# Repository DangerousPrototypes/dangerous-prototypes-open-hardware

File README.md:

# dangerous-prototypes-open-hardware
Automatically exported from code.google.com/p/dangerous-prototypes-open-hardware

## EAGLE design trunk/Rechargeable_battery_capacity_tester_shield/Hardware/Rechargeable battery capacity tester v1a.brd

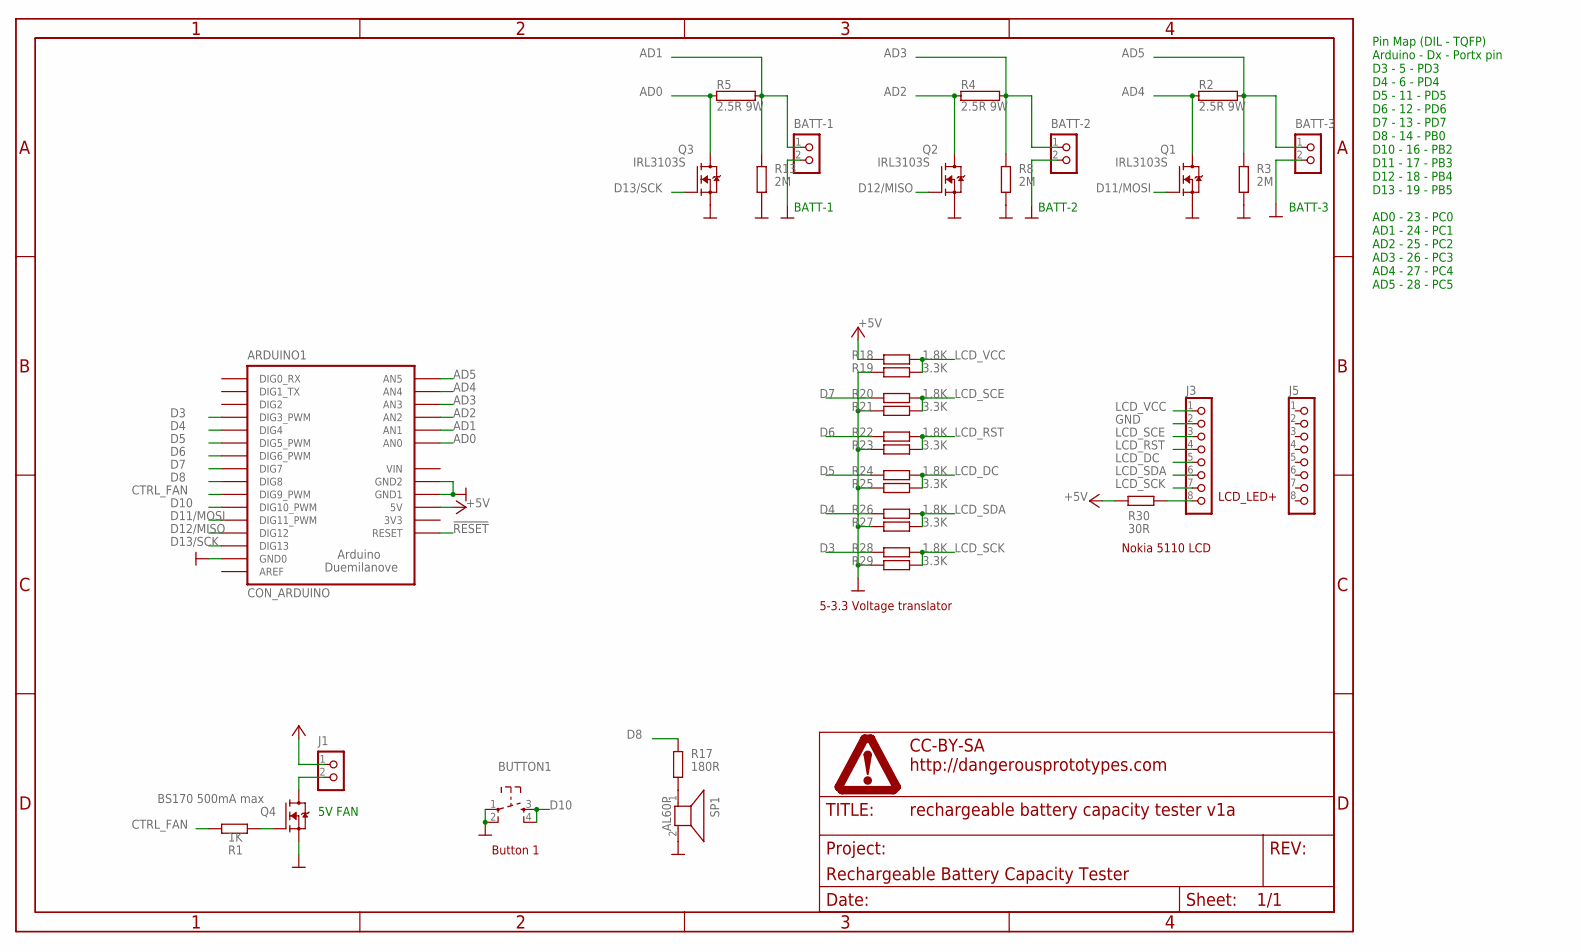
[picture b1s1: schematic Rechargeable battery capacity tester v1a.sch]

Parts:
ARDUINO1: CON_ARDUINO
BATT-1, BATT-2, BATT-3: CON_TERMINAL_BLOCK_02-5MM; TERMINAL_BLOCK_2P_5
BUTTON1: SW_TACT_4P; SW_TACT_SMALL
J1: CON_JST_2PIN-PTH; CON_JST_2PIN
J3, J5: CON_HEADER_1X08-PTH; M1X8
Q1, Q2, Q3: IRL3103S; D2PAK
Q4: BS170 500mA max; SOT-23
R1: 1K; R603
R2, R4, R5: 2.5R 9W; KH214-8
R3, R8, R13: 2M; R603
R17: 180R; R603
R18, R20, R22, R24, R26, R28: 1.8K; R603
R19, R21, R23, R25, R27, R29: 3.3K; R603
R30: 30R; R603
SP1: AL60P
U$1: FRAME_DINA4_L; DP_LOGO

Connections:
!RESET: ARDUINO1.RESET
+5V: ARDUINO1.5V, J1.1, R18.1, R30.1
AD0: ARDUINO1.A_0 (AN0), Q3.2 (D), R5.1
AD1: ARDUINO1.A_1 (AN1), BATT-1.1, R5.2, R13.2
AD2: ARDUINO1.A_2 (AN2), Q2.2 (D), R4.1
AD3: ARDUINO1.A_3 (AN3), BATT-2.1, R4.2, R8.2
AD4: ARDUINO1.A_4 (AN4), Q1.2 (D), R2.1
AD5: ARDUINO1.A_5 (AN5), BATT-3.1, R2.2, R3.2
CTRL_FAN: ARDUINO1.D_9 (DIG9_PWM), R1.1
D3: ARDUINO1.D_3 (DIG3_PWM), R28.1
D4: ARDUINO1.D_4 (DIG4), R26.1
D5: ARDUINO1.D_5 (DIG5_PWM), R24.1
D6: ARDUINO1.D_6 (DIG6_PWM), R22.1
D7: ARDUINO1.D_7 (DIG7), R20.1
D8: ARDUINO1.D_8 (DIG8), R17.2
D10: ARDUINO1.D_10 (DIG10_PWM), BUTTON1.3, BUTTON1.4
D11/MOSI: ARDUINO1.D_11 (DIG11_PWM), Q1.1 (G)
D12/MISO: ARDUINO1.D_12 (DIG12), Q2.1 (G)
D13/SCK: ARDUINO1.D_13 (DIG13), Q3.1 (G)
GND: ARDUINO1.GND0, ARDUINO1.GND1, ARDUINO1.GND2, BATT-1.2, BATT-2.2, BATT-3.2, BUTTON1.1, BUTTON1.2, J3.2, Q1.3 (S), Q2.3 (S), Q3.3 (S), Q4.2 (S), R3.1, R8.1, R13.1, R19.1, R21.1, R23.1, R25.1, R27.1, R29.1, SP1.2
LCD_DC: J3.5, R24.2, R25.2
LCD_RST: J3.4, R22.2, R23.2
LCD_SCE: J3.3, R20.2, R21.2
LCD_SCK: J3.7, R28.2, R29.2
LCD_SDA: J3.6, R26.2, R27.2
LCD_VCC: J3.1, R18.2, R19.2
unnamed: Q4.1 (G), R1.2
unnamed: J1.2, Q4.3 (D)
unnamed: J3.8, R30.2
unnamed: R17.1, SP1.1
VIN: ARDUINO1.VIN

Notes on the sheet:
Pin Map (DIL - TQFP) Arduino - Dx - Portx pin D3 - 5 - PD3 D4 - 6 - PD4 D5 - 11 - PD5 D6 - 12 - PD6 D7 - 13 - PD7 D8 - 14 - PB0 D10 - 16 - PB2 D11 - 17 - PB3 D12 - 18 - PB4 D13 - 19 - PB5 AD0 - 23 - PC0 AD1 - 24 - PC1 AD2 - 25 - PC2 AD3 - 26 - PC3 AD4 - 27 - PC4 AD5 - 28 - PC5
BATT-3
BATT-2
BATT-1
Button 1
LCD_LED+
Nokia 5110 LCD
5-3.3 Voltage translator
5V FAN

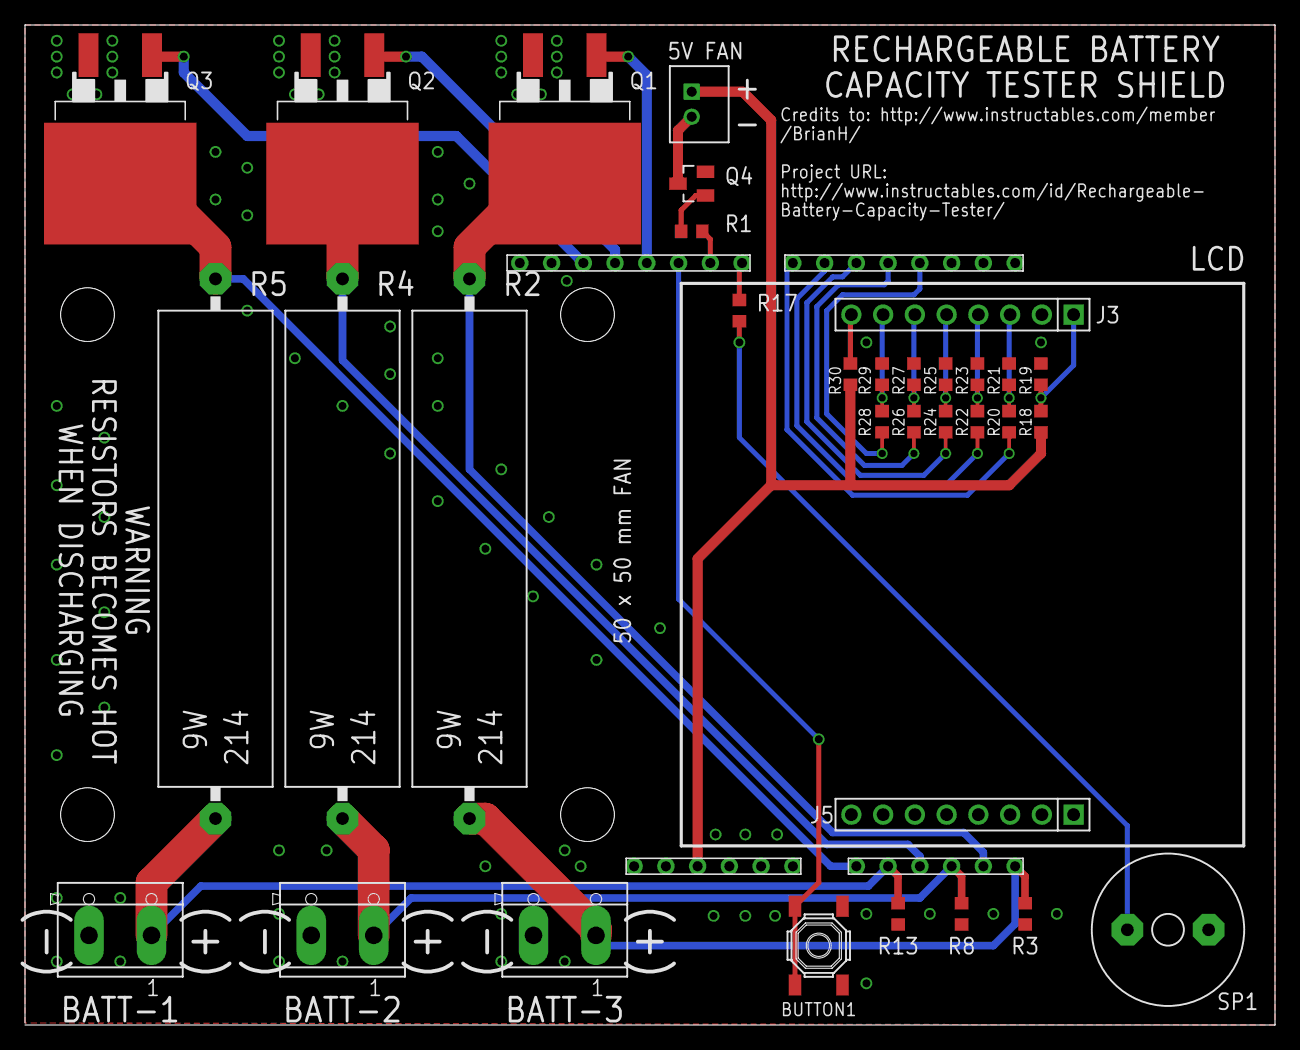
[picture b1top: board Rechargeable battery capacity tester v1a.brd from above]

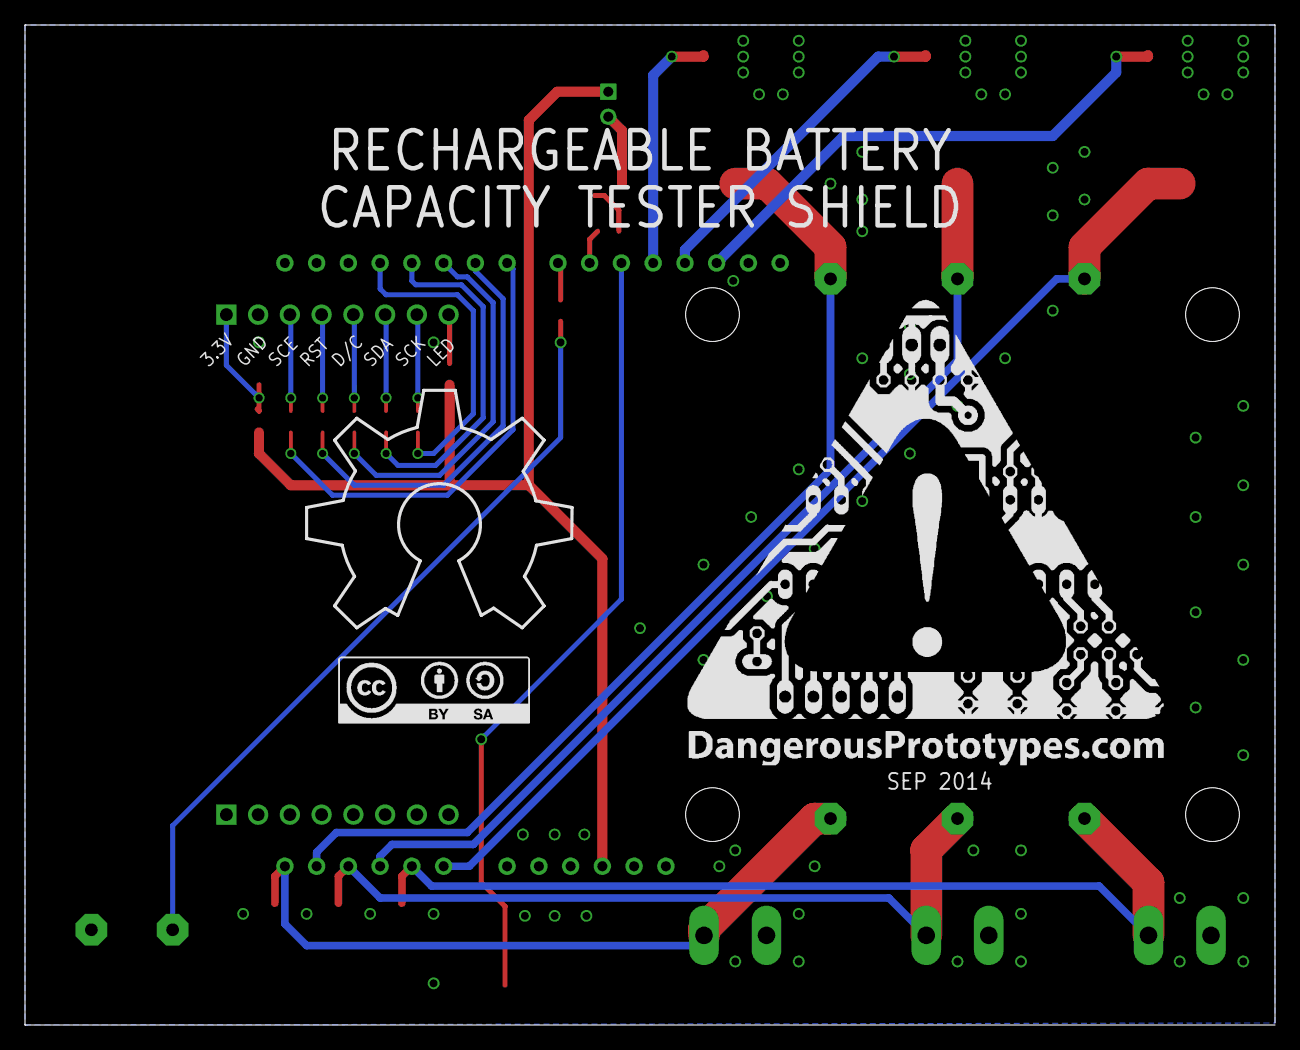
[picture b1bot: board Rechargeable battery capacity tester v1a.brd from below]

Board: 2 copper layers, 100.0 x 80.0 mm, 38 parts (3 on the bottom side), 29 nets.

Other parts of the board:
U$2: DP_LOGO_ART_1.5X1.5
U$3: LOGO_CC-BY-SA
U$4: OSHW_10X750_NOTEXT

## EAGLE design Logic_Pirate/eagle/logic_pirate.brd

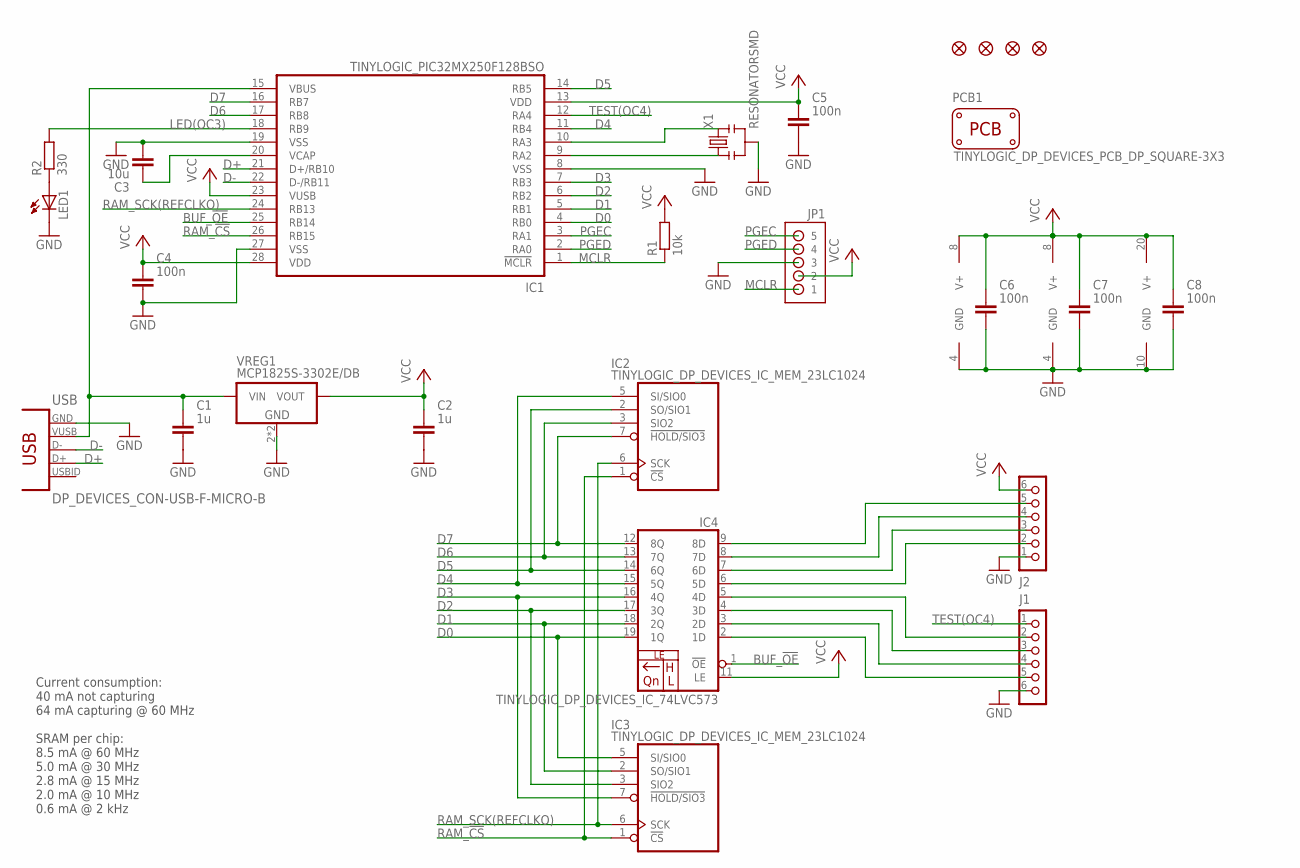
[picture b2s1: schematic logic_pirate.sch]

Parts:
C1, C2: 1u; DP_DEVICES_C603
C3: 10u; C1206
C4, C5, C6, C7, C8: 100n; DP_DEVICES_C603
IC1: TINYLOGIC_PIC32MX250F128BSO; TINYLOGIC_DP_DEVICES_SOIC-28W
IC2, IC3: TINYLOGIC_DP_DEVICES_IC_MEM_23LC1024; TINYLOGIC_DP_DEVICES_SOIC-8
IC4: TINYLOGIC_DP_DEVICES_IC_74LVC573; TINYLOGIC_DP_DEVICES_SOIC-20
J1, J2: DP_DEVICES_CON_HEADER_1X06-SMD-RIGHT-ANGLED; DP_DEVICES_M1X6_MALE_RIGHT_ANGLED_SMD
JP1: TINYLOGIC_CHIPKIT_UNO32_MECHANICAL_HDR-1X5-OFFSET; TINYLOGIC_CHIPKIT_UNO32_MECHANICAL_HDR-1X6_OFFSET
JP2, JP3, JP4, JP5: FIDUCIAL1X2; FIDUCIAL-1X2
LED1: Status; CHIPKIT_UNO32_DISCRETE_D0603
PCB1: TINYLOGIC_DP_DEVICES_PCB_DP_SQUARE-3X3; TINYLOGIC_DP_DEVICES_DP3030_V1
R1: 10k; DP_DEVICES_R603
R2: 330; DP_DEVICES_R603
USB: DP_DEVICES_CON-USB-F-MICRO-B; DP_DEVICES_CONN_USB_MICRO-B
VREG1: MCP1825S-3302E/DB; DP_DEVICES_SOT-223
X1: RESONATORSMD; RESONATOR-SMD

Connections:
BUF_!OE!: IC1.25 (RB14), IC4.1 (!OE)
D0: IC1.4 (RB0), IC3.5 (SI/SIO0), IC4.19 (1Q)
D1: IC1.5 (RB1), IC3.2 (SO/SIO1), IC4.18 (2Q)
D2: IC1.6 (RB2), IC3.3 (SIO2), IC4.17 (3Q)
D3: IC1.7 (RB3), IC3.7 (!HOLD/SIO3), IC4.16 (4Q)
D4: IC1.11 (RB4), IC2.5 (SI/SIO0), IC4.15 (5Q)
D5: IC1.14 (RB5), IC2.2 (SO/SIO1), IC4.14 (6Q)
D6: IC1.17 (RB8), IC2.3 (SIO2), IC4.13 (7Q)
D7: IC1.16 (RB7), IC2.7 (!HOLD/SIO3), IC4.12 (8Q)
D+: IC1.21 (D+/RB10), USB.P3 (D+)
D-: IC1.22 (D-/RB11), USB.P2 (D-)
GND: C1.2, C2.2, C3.2, C4.2, C5.2, C6.2, C7.2, C8.2, IC1.8 (VSS), IC1.19 (VSS), IC1.27 (VSS), IC2.4 (GND), IC3.4 (GND), IC4.10 (GND), J1.6, J2.1, JP1.3, LED1.C, USB.P5 (GND), VREG1.2 (GND), VREG1.4 (GND), X1.2
LED(OC3): IC1.18 (RB9), R2.2
MCLR: IC1.1 (!MCLR), JP1.1, R1.1
unnamed: IC4.2 (1D), J1.5
unnamed: IC4.3 (2D), J1.4
unnamed: IC4.4 (3D), J1.3
unnamed: IC4.5 (4D), J1.2
unnamed: IC4.6 (5D), J2.2
unnamed: IC4.7 (6D), J2.3
unnamed: IC4.8 (7D), J2.4
unnamed: IC4.9 (8D), J2.5
unnamed: LED1.A, R2.1
unnamed: IC1.10 (RA3), X1.3
unnamed: IC1.9 (RA2), X1.1
unnamed: C3.1, IC1.20 (VCAP)
PGEC: IC1.3 (RA1), JP1.5
PGED: IC1.2 (RA0), JP1.4
RAM_!CS!: IC1.26 (RB15), IC2.1 (!CS), IC3.1 (!CS)
RAM_SCK(REFCLKO): IC1.24 (RB13), IC2.6 (SCK), IC3.6 (SCK)
TEST(OC4): IC1.12 (RA4), J1.1
VBUS: C1.1, IC1.15 (VBUS), USB.P1 (VUSB), VREG1.1 (VIN)
VCC: C2.1, C4.1, C5.1, C6.1, C7.1, C8.1, IC1.13 (VDD), IC1.23 (VUSB), IC1.28 (VDD), IC2.8 (V+), IC3.8 (V+), IC4.11 (LE), IC4.20 (V+), J2.6, JP1.2, R1.2, VREG1.3 (VOUT)

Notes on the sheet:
Current consumption: 40 mA not capturing 64 mA capturing @ 60 MHz SRAM per chip: 8.5 mA @ 60 MHz 5.0 mA @ 30 MHz 2.8 mA @ 15 MHz 2.0 mA @ 10 MHz 0.6 mA @ 2 kHz

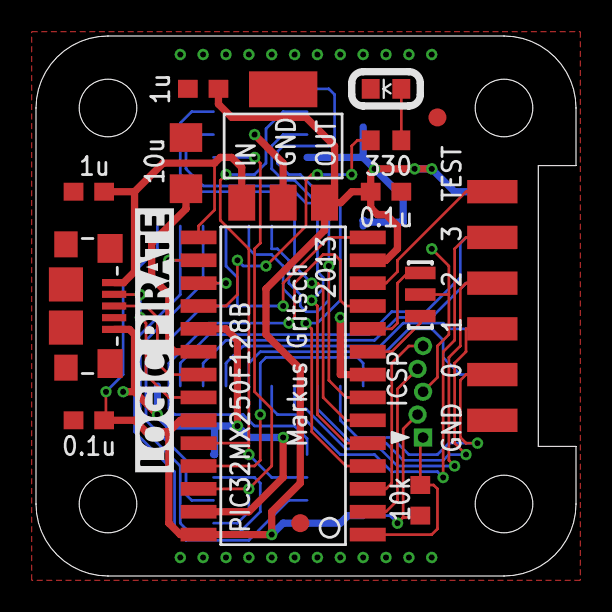
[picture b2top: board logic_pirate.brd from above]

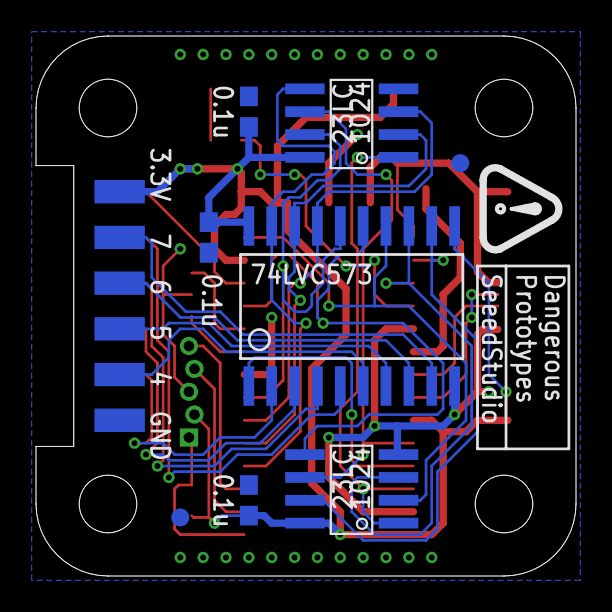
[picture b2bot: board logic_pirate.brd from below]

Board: 2 copper layers, 30.0 x 30.0 mm, 28 parts (10 on the bottom side), 33 nets.

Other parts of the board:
U$1: LP_LOGO
U$4: TINY_LOGO

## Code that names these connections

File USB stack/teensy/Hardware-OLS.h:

/*
*
*	Open Logic Sniffer firmware v1.1
*	http://www.gadgetfactory.net
*	http://dangerousprototypes.com
*	License: GPL
*	Copyright Ian Lesnet 2010
*
*/
#ifndef HARDWARE_PROFILE_H
#define HARDWARE_PROFILE_H

//the first batch of OLS has 20mhz crystal on the PIC
//use this to compile for that hardware
#define XTAL_20MHZ

//hardware version string
#define HW_VER 0x01

//firmware version string
#define FW_VER_H 0x00
#define FW_VER_L 0x06

//Define to enable manufacturing hardware 
//self-test with jumper check on UART header.
//If there is a jumper between RX and TX
//the firmware will light the ACT LED and send 0x03 
//to the FPGA through the UART. THis triggers a test mode
//in special bitstream builds.
#define SELF_TEST	

//measure the voltage on PROG_B (AN3/RA3), should be 2.5volts
#define VREG_TEST
//calculate the ADC value to test for
//#define ADC_2V5 ((25/33)*1024) //2.5volts/3.3volts * 1024 = ADC reading (775.75).
//#define ADC_2V5_LIMIT (ADC_2V5-(ADC_2V5/10)) //show error if not within 10% 775-78=697
#define ADC_2V5_LIMIT 697

//During testing we used a pin for the UART 
// that was sharted with a trigger pin
// some old bitstreams used it and it got confusing
//We had to keep changing it back and forth so I added this define
//There isn't really any reason you should ever need this, 
// especially in the SPI version, but here it is. Enjoy.
//#define OLDRXPIN //use RX on the old pin

//pin setup
/*
A0 PR0 flash_si
A1 PR1 flash_so
A2 flash_cs
A3 PROG_B (pull-down only) test high
A5 RP2 DONE (input only) test high, eventually
C1 RP12 update button (input/interrupt) test high
C2 RP13 ACT LED

B7 RP10 PGD
B6 RP9 PGC
B5 RP8 flash_sck
B4 RP7 FPGA_AUX0
B3 RP6 fpga_cs
B2 RP5 fpga_aux1
B1 RP4 FPGA_AUX2
B0 RP3 FPGA_AUX3
C7 RP18 RX1
C6 RP17 TX1
*/
#define PIN_PROG_B 		PORTAbits.RA3
#define TRIS_PROG_B 	TRISAbits.TRISA3
#define PROG_B_LOW()	PIN_PROG_B=0; TRIS_PROG_B=0 //ground,output
#define PROG_B_HIGH()	PIN_PROG_B=0; TRIS_PROG_B=1	

#define PIN_DONE		PORTAbits.RA5
#define PIN_UPDATE 		PORTCbits.RC1
#define PIN_LED			PORTCbits.RC2

#define TRIS_UART1_TX	TRISCbits.TRISC6
#define PIN_UART1_TX	LATCbits.LATC6
#define TRIS_UART1_RX	TRISCbits.TRISC7
#define PIN_UART1_RX	PORTCbits.RC7
//	#define TRIS_UART1		TRISC
//	#define TXPIN_UART1		0b01000000
//	#define RXPIN_UART1		0b10000000

#define TRIS_UART2_TX	TRISBbits.TRISB1
#define PIN_UART2_TX	PORTBbits.RB1

#define TRIS_FLASH_SCK	TRISBbits.TRISB5
#define PIN_FLASH_SCK	PORTBbits.RB5
#define TRIS_FLASH_MOSI	TRISAbits.TRISA0
#define PIN_FLASH_MOSI	PORTAbits.RA0

#define TRIS_FLASH_CS	TRISAbits.TRISA2
#define PIN_FLASH_CS	PORTAbits.RA2
#define FPGA_CS_LOW()	PIN_FLASH_CS=0; TRIS_FLASH_CS=0
#define FPGA_CS_HIGH() 	PIN_FLASH_CS=1; TRIS_FLASH_CS=0

#define TRIS_FPGA_SCK	TRISBbits.TRISB4
#define PIN_FPGA_SCK	PORTBbits.RB4
#define TRIS_FPGA_MISO	TRISBbits.TRISB2
#define PIN_FPGA_MISO	PORTBbits.RB2
#define TRIS_FPGA_MOSI	TRISBbits.TRISB3
#define PIN_FPGA_MOSI	PORTBbits.RB3
#define TRIS_FPGA_DATAREADY	TRISBbits.TRISB1
#define PIN_FPGA_DATAREADY	PORTBbits.RB1

#define TRIS_FPGA_CS	TRISAbits.TRISA1
#define PIN_FPGA_CS		PORTAbits.RA1

#define BootloaderJump() _asm goto 0x16 _endasm

//these are unneeded, but the stack complains if they're not defined
//#define USE_SELF_POWER_SENSE_IO
#define tris_self_power     TRISCbits.TRISC2    
#define self_power          1

//#define USE_USB_BUS_SENSE_IO
#define tris_usb_bus_sense  TRISCbits.TRISC2    
#define USB_BUS_SENSE       1 

#endif 

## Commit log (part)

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2012-08-14 Changes to USB interrupt from JTR
2012-08-14 small fix to BPv4 bootloader (comment in wrong place)
    http://dangerousprototypes.com/forum/viewtopic.php?f=28&t=3441&start=45#p42466
2012-08-14 Added USB interrupt fix to BPv4 from: http://dangerousprototypes.com/forum/viewtopic.php?f=28&t=3441&start=45#p42038
2012-08-16 Bus Pirate Demo board firmware
2012-08-20 Added device: 23LC1024 SRAM in SOIC-8
2012-08-27 update to blog theme with header fix, switch for contest theme.
2012-08-27 blog theme contest template update
2012-09-04 Added devices: 74HC595 and 74141 Added footprint: DIL16 Updated: removed extra mounting holes on DP6060 Added schematic symbol: 12V, -12V and -5V Added Logo: Flame logo
2012-09-04 revised credit card sized PCB based on ISO.IEC 7810 ID-1 identification cards sizes, size changed from 85 x 56 mm to 85.60 x 53.98 mm
2012-09-05 SU originals for the ATX case laser cutting
2012-09-06 little file reshuffeling in the ATX laser cutt files
2012-09-07 Fix IN-12 socket, replaced with correct cutout.
2012-09-07 Added: IN-12 Nixie tube display, IN-12 Socket cutout footprint Fixed: IN-12 Socket
2012-09-12 Updated ATX PSU v1.3 Added ATX PSU v2 board. Board was made in KiCAD
2012-09-12 first commit of DP KiCAD part library
2012-09-13 .lib and .mod files converted using eagle2kicad-0.d.ulp from http://www.modulbot.com/download.html Fixed undefined DRAW command when loading to symbol library to KiCAD
2012-09-17 add bus pirate v5c board, enlarge ADC Input label
2012-09-20 Bus Pirate v4 Sick of Beige case laser cutting files and partlist(BOM)
2012-09-21 SoB case generator plugin from Tayken
2012-09-24 Done the changes related to global->instance variables suggested by Jim, corrected some variable name typos and got rid of console debug messages.
2012-09-24 Added new Logic shrimp v2b, this version uses 23LC1024 SRAM
2012-09-25 added direction info on birectional buffer ICs
2012-09-25 Board files
2012-09-25 add schematic image
2012-09-27 OHS 2012 presentations
2012-10-01 Smoke Tester 3D model and renders
2012-10-07 Adding a vertical ATX socket from the Molex MiniFit Jr. line.
    Discrete sockets (key'ed and rectangular) are provided in separate files so they can be easily added to create different configurations. Each socket is made to be "stackable" on both sides, so you'll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
2012-10-07 adding an assortment of 3d models. They should all have origins centered properly about the pins. These were not checked thoroughly, but do appear to be generally correct. Most models are tweaked fro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
    The QFN32 is original and should be extremely easy to scale and accommodate other numbers of pins.
2012-10-08 Added: D8035E VFD board, composed of 3 boards. Board A, B and C
2012-10-08 Added: PTH variant of 2.1mm DC Barrel Connector with milled hole pads
2012-10-09 added series diode on Vusb in and Vin header, moved C8 beside SD holder
2012-10-10 first cut at molex KK series connectors. The 1x2 should be modeled in such a way that it's side stackable, so it will be easy to make additional even numbered connectors. These were based on a model 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
    These should be "close enough" for most purposes, alignment appears to be off a bit on the 4pos header though.
2012-10-10 Bourns TC33X-2-104E 3mm surface mount trim pot
2012-10-10 Added: 3D models for 2 trough-hole IC and a metalized Capacitor.
2012-10-11 added version 2
2012-10-16 rearanged SID SVN, and aded the mauf resources and sales page foleder...as wlell as the sales page txt
2012-10-18 correcting the naming for the 2512 resistor model
2012-10-18 adding a 2010 resistor
2012-10-18 Bus Blaster v4 test buffer project
2012-10-18 Bus blaster v3 v4 manufacturing resrouces
2012-10-22 Soldering Iron Driver renderings and 3D model
2012-10-25 Added projects: DP6037 protoboard v1, DP6037_PTH v1 and DP6037_SMD v1
2012-10-25 add: FT230x_LTC4053_BB
2012-10-25 Add project: FT311 breakout board v1b
2012-10-28 Retrieved demo board v5 files from previous revision, and renamed the wrongly named v5a into proper names
2012-10-30 added DIL-28 PTH to SMD socket
2012-10-31 Added manufacturing files for updated ATX board acrylic case
2012-11-05 added: 4.5 x 4.5 SMD Trimmer, model 3314G
2012-11-07 added right angled 0.1inch 1x06 male header. expanded M1X4, M1X6, M1X8 pads to 1.632mm and drill size to 1.02mm
2012-11-13 added a 1x06 right angled header and a 2x03 SMD straight male headers.
2012-11-15 initial xQFP protoboards folder
2012-11-19 BP v4d, buspirate v4 fitted into a bigger DP PCB (DP7043)
2012-11-22 added ICSP with pogo pin as connector
2012-11-22 fix, ICSP pogo pin programmer footprint by adding a pad on the keyhole for a key pogo pin to be soldered
2012-11-30 added 0.50, 0.65 and 0.80 mm pitch universal QFP footprint and QFP breakout board These footprint are licensed: CC-BY-SA
2012-12-06 added protoboard with 0.50mm xQFP
2012-12-06 added protoboard with 0.65mm and 0.80mm xQFP
2012-12-07 updated 0.5, 0.65 and 0.8 xQFP protoboards by adding a USB footprint. 2-3 SOT-23-6 footprints were removed to fit the usb
2012-12-07 widen pad diameter
2012-12-12 added dual xQFP pitch protoboards, pitch combined are 0.50 + 0.65 mm, 0.80 + 0.50 mm and 0.80 + 0.65 mm. these boards were also having a micro usb footprint under its mini-b footprint
2012-12-12 adding dual pitch back to back footprint on xQFP breakout, combined pitch are 0.50 + 0.65, 0.80 + 0.50 and 0.80 + 0.65 mm QFP
2012-12-14 fix pad, changed via to a pad. new board named v1b
2012-12-20 added: 1x1 PTH hole for protoboard filler changed "board name" of DP standard PCB name(on the bottom) to ">NAME" so it will now be smashable a can be moved around.
2012-12-20 revert back DP Standard PCB with the label name indicating its PCB size
2013-01-07 added 0603 SMD LED, 1x02 and 1x03 right angled 0.1 inch pitched PTH header
2013-01-08 renamed xQFP_protoboard_080_050.v1 to v2
2013-01-10 Bus Pirate - AUXpin.c. Cleaned the code a bit, deleted a huge commented out section, and applyed the patch in issue #65 http://dangerousprototypes.com/track/view.php?id=65
2013-01-11 Bus Pirate firmware -v4 pull up voltage control add to bin protocol. as per issue 63 http://dangerousprototypes.com/track/view.php?id=63 patch available at the link above, and is applied to rev2082
2013-01-14 A slight change in variable definition in procMenu.c, and indent fix in I2C.c
2013-01-16 Bus Pirate firmware issue 51 minor fix to the protos function pointer array, in the BP_USE_I2C section. nulfunc changed to I2Cstop.. http://dangerousprototypes.com/track/view.php?id=51
2013-01-18 HEx files ready for upload through bootloader for BP v3 and v4 6.3r2088
2013-01-22 Bus Pirate firmware - issue 50 added support for RAW mode as well, entered through 'w'
    so now it;s rd foe decimal, rx for HEX, rb for BIN and rw for raw
2013-01-25 Test commit.
2013-01-25 Test
2013-01-25 * Added bootloader.
2013-01-25 * Added bootloadable firmware.
2013-01-26 * Added ZIP packages.
2013-01-27 * Added color scheme for logic shrimp probe cables.
2013-01-31 Bus Pirate Firmware issue #89 - adding UART communications in debugging mode, to activate, #define BPV4_DEBUG, to deactivate comment it out in base.h.. This lets you to connect your debugger and run 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
2013-01-31 * Implemented META command.
2013-02-01 * Improved META command.
2013-02-11 fix ICSP 0.1 inch header pin 5 made it to a circular pad. added proto pads with 1.2mm diameter drills
2013-02-18 add: PTH ferrite bead 10mm pitch, 20x20mm 8x8 LED matrix
2013-02-19 Mark pin 1 of DIP8, DIP14, DIP14W as this is automatically changed to a square pad by DRC check. Corrected SO-8's name and values labels to their proper layers
2013-02-19 Bus blaster v3 manufacturing test package
2013-02-19 update parts list of v3c and v4.1a, copied updated parts list to /hardware folder, made manufacturing resources files for v4.1.
2013-02-21 add BP v3.8 I/O arrangement changed to 5V - GND VPU - 3V3 AUX - ADC MISO - CS MOSI - CLK
2013-03-07 updates on v3.8 USB connector now in micro-B All SMD LEDs are in LED603 IO shrouded header fix, notch is facing outward not much change on the USB D+ D- line just did route them to have almost the sa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
2013-03-07 IO pinout re-arrange to be like bpv4
2013-03-11 Added single pad with 40mil and 32 mil drill size both square and round Added SOIC 14W, 18W, 8NW, 14NW and 16NW footprints N-narrow, W-wide, NW - Narrow + Wide Added 10cm x 10cm (DP100100) in SoB
2013-03-13 change U3 of parts list from a 44 pin to 100 pin XC2C64A-7VQG100C CPLD
2013-03-14 I know the SPI module works with the changes made to the underlying communication tools. However, all the other modules need some verification. I'll probably try to put together some unit-tests. Howe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
2013-03-15 added 24AA04 DIP, 25AA04, MCP3001, MCP4901, MCP9701, TC74 TO220-5 fix some text on POT symbol
2013-03-18 Bus Pirate firmware - commented out #define BPV4_DEBUG so it's in normal mode by default
2013-04-03 Added: MCP4131 Digital Potentiometer Tester Probe socket QFN 12 and 16 pins 3x3cm QFN 16, 20 and 24 4x4 cm SOIC Narrow+Wide 18, 20, 24 and 28 pins
2013-04-16 Added board files
2013-04-23 added gerbmerge config creator ULP
2013-04-26 fix project multiple default to zero when project multiple spinbox is not touched
2013-05-08 moved anchor/reference point of SoB PCBs to its center
2013-06-23 * Updated version info.
2013-06-25 * Improved USB command parsing.
2013-07-23 Added: MCP7940 I2C RTC with SRAM in SOIC8 and DIP8, Alternate 3 Pins Voltage Regulator to accomodate 4th pin as tab connection. Revised VREG 3 PINS now with TO-220 Horizontal footprint
2013-07-24 bus pirate: fix slashes and filename case for linux compatibility
2013-09-28 merging PyBusPirateLite branch back into mainline
2014-01-10 changed SMD SMC-A pad size from 1.60 x 1.40 to 1.40 x 1.80 changed SMD SMC-B pad size from 1.60 x 2.40 to 1.40 x 2.80 added new SMD SMC-C footprint added part MBI5026 (SOIC-24 variant) 16-Bit constan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
2014-02-03 Stepper motor driver based on Linistepper v2.0 (http://www.romanblack.com/lini.htm)
2014-02-11 SMD Tape cutting controller intended to automatically dispense SMD parts
2014-02-11 wrong folder
2014-02-11 uploaded directories and files
2014-02-23 SPI mode } command was giving errors, busPirateCore.c line 225 now maps to SPIstop for stopR. Should fix it. Untested.
2014-03-21 correct EEPROM for v2/2.5, v3c and v4a, old EEPROM value was non 3.3V compliant (93C46), replaced with 93LC46B. updated schematic, wiki, BOM/Partlist. Board and gerbers still the same
2014-03-23 changed VR1, VR2 LDO regulators to MCP1801T-3302I/OT and VR3 to MCP1801T-5002I/OT. to fix the issue on LDO output voltage oscillation due to the usage of ceramic caps on the output of each LDO. these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
2014-08-22 Fix for http://dangerousprototypes.com/forum/viewtopic.php?f=4&t=6667
2014-08-28 added bus pirate v3.8a a compact bus pirate v3.8 fitted within 5x5cm SoB board
2014-08-29 -added library for version 6, keeping older version as is for older kicad users
2014-09-03 board update: -changed ICSP header to 6pins, spare pin not connected -moved all LEDs a little to the right for even space
2014-09-03 committing initial files
2014-09-04 -fix the overlapping resistors (R2 and LCD SMT voltage dividers resistors)
2014-11-04 various parts added
2015-08-28 Migrating wiki contents from Google Code
2017-04-30 Fix rescue lib
2017-05-15 Update for python3
    Now the script detects whether it is being executed under python 3.X or python 2.X.
2019-09-15 @makaveli344
    Deep quantum time machine xpapi

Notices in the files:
trunk/Rechargeable_battery_capacity_tester_shield/Hardware/Rechargeable battery capacity tester v1a.brd:
LICENSE: CC-BY-SA
